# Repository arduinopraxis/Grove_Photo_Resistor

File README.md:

# Grove_Photo_Resistor
Grove Photo Resistor (LDR) with I2C interface

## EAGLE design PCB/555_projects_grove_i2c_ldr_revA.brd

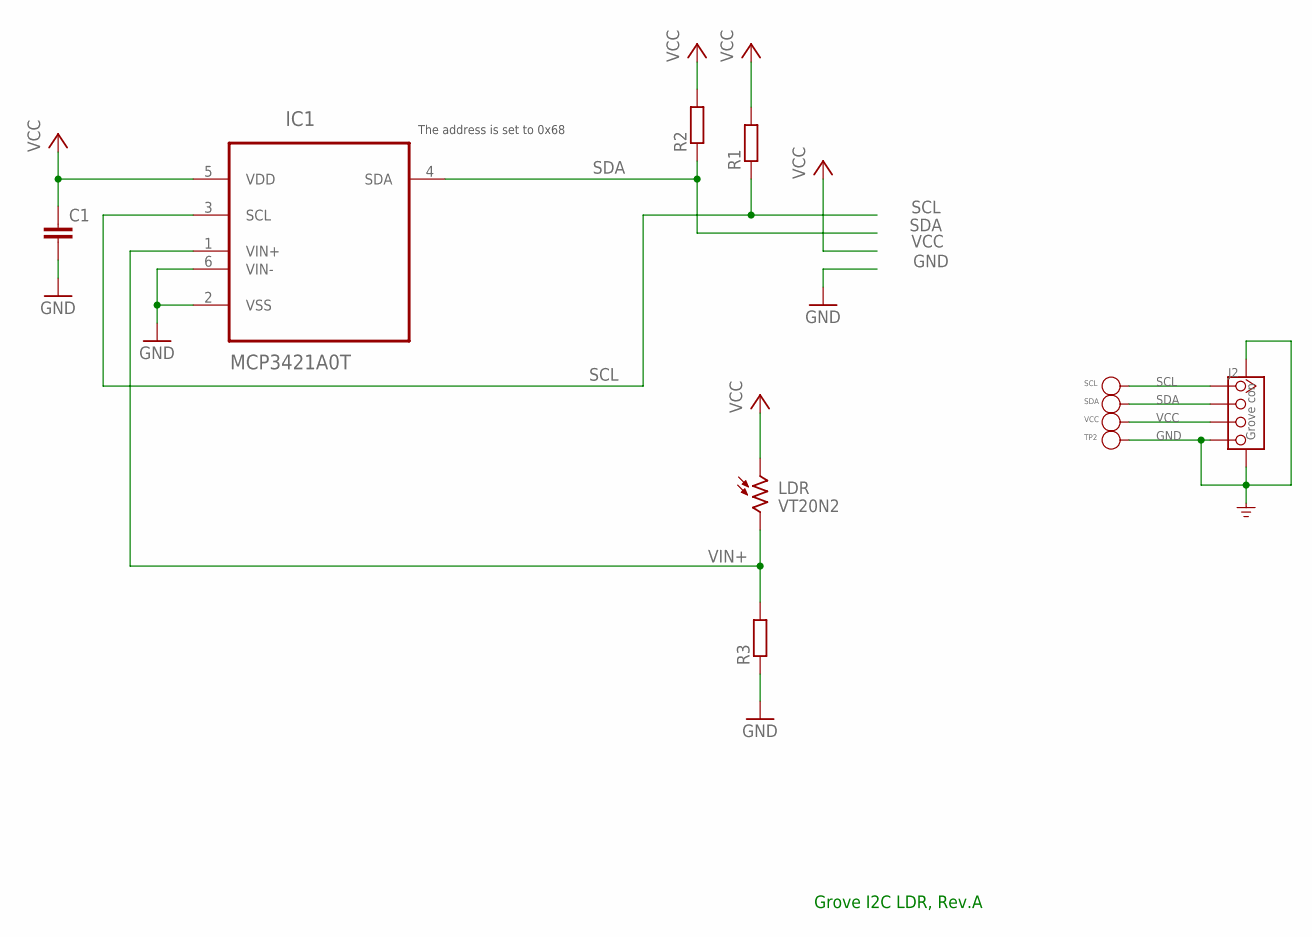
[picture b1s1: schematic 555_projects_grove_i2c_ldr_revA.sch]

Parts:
C1: C-EUC0805K; C0805K
IC1: MCP3421A0T; SOT95P270X145-6N
J2: Grove con; 4P-SMD-2.0
LDR: VT20N2; TO46-VT200
R1, R2, R3: R-EU_R0805; R0805
SCL: TP3; TP_4545
SDA: TP3; TP_4545
TP2: PAD-TEST-POINT'4545'; TP_4545
VCC: TP2; TP_4545

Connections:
GND: C1.2, IC1.2 (VSS), IC1.6 (VIN-), J2.4, J2.SS1, J2.SS2, R3.1, TP2.T
SCL: IC1.3 (SCL), J2.1, R1.1, SCL.T
SDA: IC1.4 (SDA), J2.2, R2.1, SDA.T
VCC: C1.1, IC1.5 (VDD), J2.3, LDR.1, R1.2, R2.2, VCC.T
VIN+: IC1.1 (VIN+), LDR.2, R3.2

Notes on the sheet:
The address is set to 0x68
Grove I2C LDR, Rev.A

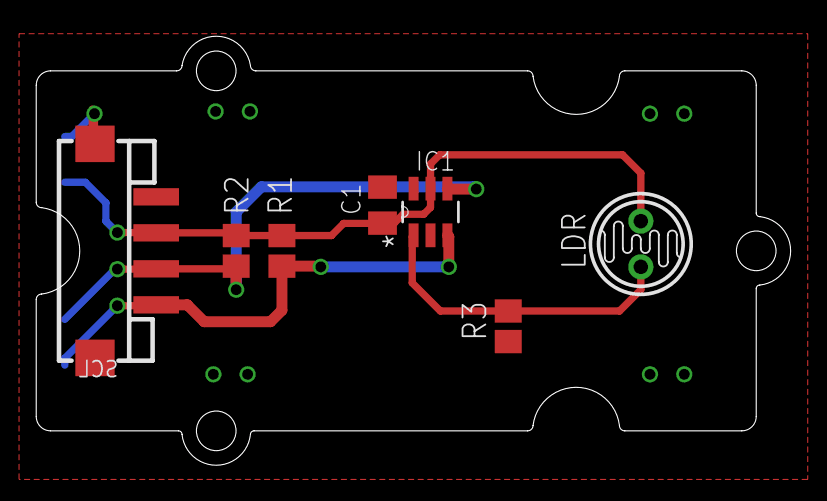
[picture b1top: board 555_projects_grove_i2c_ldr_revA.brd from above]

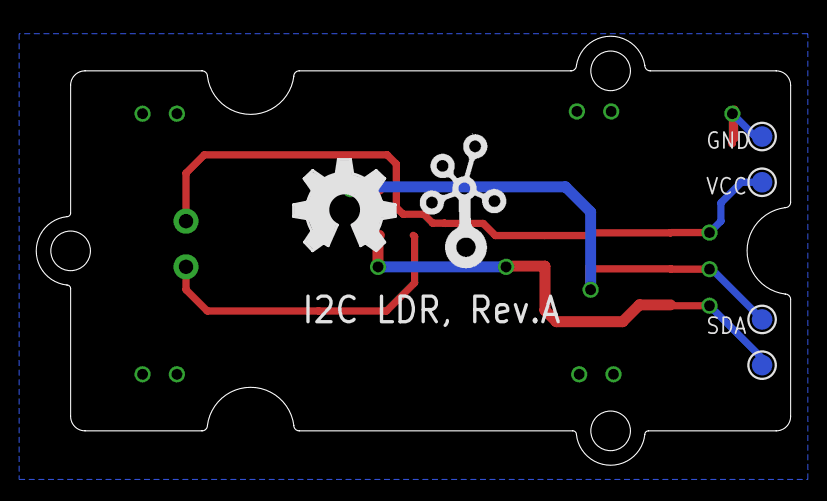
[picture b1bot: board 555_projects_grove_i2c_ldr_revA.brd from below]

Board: 2 copper layers, 41.9 x 23.8 mm, 14 parts (6 on the bottom side), 5 nets.

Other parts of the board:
U$9: GROVE-2CONNECTOR-SMD
U$11: TWIGLOGO
U$12: OSHW_FILLX200_NOTEXT
